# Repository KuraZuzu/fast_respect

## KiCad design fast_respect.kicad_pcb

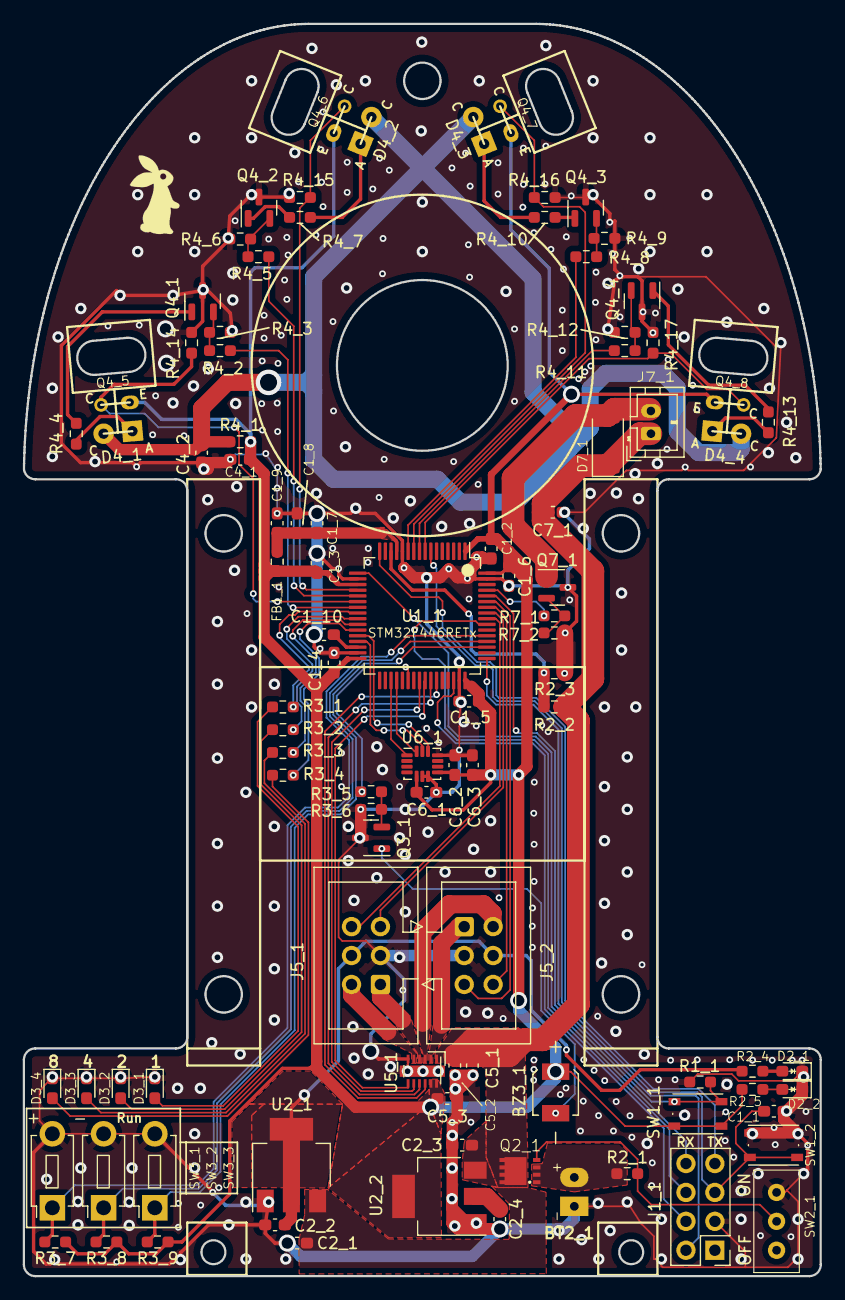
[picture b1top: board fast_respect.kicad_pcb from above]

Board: 2 copper layers, 70.0 x 110.0 mm, 97 parts (0 on the bottom side), 72 nets.

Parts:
BT2_1: Battery; 2sBattery
BZ3_1: SMT-0440-T-HT-R; XDCR_SMT-0440-T-HT-R
C1_1, C1_3, C1_4, C1_5, C1_6, C1_8, C5_2, C5_3, C6_2: 0.1uF; C_0603_1608Metric_Pad1.08x0.95mm_HandSolder
C1_2, C1_10: 4.7uF; C_0603_1608Metric_Pad1.08x0.95mm_HandSolder
C1_7, C6_1: 0.01uF; C_0603_1608Metric_Pad1.08x0.95mm_HandSolder
C1_9, C4_1, C4_2: 1uF; C_0603_1608Metric_Pad1.08x0.95mm_HandSolder
C2_1, C2_3, C5_1, C7_1: 10uF; C_0603_1608Metric_Pad1.08x0.95mm_HandSolder
C2_2, C2_4: 22uF; C_0603_1608Metric_Pad1.08x0.95mm_HandSolder
C6_3: 2.2uF; C_0603_1608Metric_Pad1.08x0.95mm_HandSolder
D2_1: LED_R; LED_0603_1608Metric_Pad1.05x0.95mm_HandSolder
D2_2: LED_Y; LED_0603_1608Metric_Pad1.05x0.95mm_HandSolder
D3_1: LED_B1; LED_0603_1608Metric_Pad1.05x0.95mm_HandSolder
D3_2: LED_B2; LED_0603_1608Metric_Pad1.05x0.95mm_HandSolder
D3_3: LED_B3; LED_0603_1608Metric_Pad1.05x0.95mm_HandSolder
D3_4: LED_B4; LED_0603_1608Metric_Pad1.05x0.95mm_HandSolder
D4_1, D4_2, D4_3, D4_4: SFH4550; DIstance-Sensor_LED_D5.0mm
D7_1: RB080LAM-30TR; D_SOD-128
FB1_1: FerriteBead; R_0603_1608Metric
J1_1: Conn_02x04_Odd_Even; PinHeader_2x04_P2.54mm_Vertical
J5_1, J5_2: Conn_02x03_Odd_Even; IDC-Header_2x03_P2.54mm_Vertical
J7_1: Conn_01x02; JST_PH_B2B-PH-K_1x02_P2.00mm_Vertical
Q2_1: AONM7421; AON7421
Q3_1, Q4_1, Q4_2, Q4_3, Q4_4, Q7_1: IRLML6344T; SOT-23
Q4_5, Q4_6, Q4_7, Q4_8: ST-1KL3A; DIstance-Sensor_PHTR_D5.0mm
R1_1, R3_6, R4_3, R4_6, R4_9, R4_12, R7_2: 10k; R_0603_1608Metric_Pad0.98x0.95mm_HandSolder
R2_1: 100k; R_0603_1608Metric_Pad0.98x0.95mm_HandSolder
R2_2: 2k; R_0603_1608Metric_Pad0.98x0.95mm_HandSolder
R2_3, R3_7, R3_8, R3_9, R4_14, R4_15, R4_16, R4_17: 1k; R_0603_1608Metric_Pad0.98x0.95mm_HandSolder
R2_4: 620; R_0603_1608Metric_Pad0.98x0.95mm_HandSolder
R2_5: 280; R_0603_1608Metric_Pad0.98x0.95mm_HandSolder
R3_1, R3_2, R3_3, R3_4: 100; R_0603_1608Metric_Pad0.98x0.95mm_HandSolder
R3_5, R4_2, R4_5, R4_8, R4_11, R7_1: 10; R_0603_1608Metric_Pad0.98x0.95mm_HandSolder
R4_1: 20; R_0603_1608Metric_Pad0.98x0.95mm_HandSolder
R4_4, R4_7, R4_10, R4_13: 1; R_0603_1608Metric_Pad0.98x0.95mm_HandSolder
SW1_1: BOOT0_SW; SW_Push_1P1T_NO_Vertical_Wuerth_434133025816
SW1_2: NRST_SW; SW_Push_1P1T_NO_Vertical_Wuerth_434133025816
SW2_1: SW_SPDT; SW_Slide_SS12D01G4_AKIZUKI
SW3_1, SW3_2, SW3_3: SW_Push; SW_PUSH_1P1T_6x3.5mm_H4.3_APEM_MJTP1243
U1_1: STM32F446RETx; LQFP-64_10x10mm_P0.5mm
U2_1: AZ1117-5.0; SOT-223-3_TabPin2
U2_2: AZ1117-3.3; SOT-223-3_TabPin2
U5_1: DRV8835DSSR; DRV8835_ThermalExpanded_WSON-12-1EP
U6_1: ICM-42688-P; LGA-14_ExpandPad_3x2.5mm_P0.5mm_LayoutBorder3x4y

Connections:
+3.3V: BZ3_1.LOAD+, C1_2.2, C1_3.2, C1_4.2, C1_5.2, C1_6.2, C2_4.1, C4_1.1, C5_3.2, C6_1.1, C6_2.1, C6_3.1, FB1_1.2, Q4_5.1 (C), Q4_6.1 (C), Q4_7.1 (C), Q4_8.1 (C), R2_5.1, R3_7.1, R3_8.1, R3_9.1, R4_1.2, SW1_1.1, U1_1.1 (VBAT), U1_1.19 (VDD), U1_1.32 (VDD), U1_1.48 (VDD), U1_1.64 (VDD), U2_2.2 (VO), U5_1.11 (Mode), U5_1.12 (VCC), U6_1.5 (VDDIO), U6_1.8 (VDD)
+5V: C2_2.1, J5_1.4, J5_2.4, R2_4.1, U2_1.2 (VO)
+8V: C2_1.1, C2_3.1, C5_1.2, C5_2.1, C7_1.1, D7_1.1 (K), J7_1.1, Q2_1.3 (D), R2_2.1, U2_1.3 (VI), U2_2.3 (VI), U5_1.1 (VM)
BAT_ADC: R2_2.2, R2_3.1, U1_1.14 (PA0)
BOOT0: R1_1.1, SW1_1.2, U1_1.60 (BOOT0)
BUZZER_PWM: R3_5.1, U1_1.38 (PC7)
DIST_ADC_1: Q4_5.2 (E), R4_14.1, U1_1.22 (PA6)
DIST_ADC_2: Q4_6.2 (E), R4_15.1, U1_1.20 (PA4)
DIST_ADC_3: Q4_7.2 (E), R4_16.1, U1_1.10 (PC2)
DIST_ADC_4: Q4_8.2 (E), R4_17.1, U1_1.8 (PC0)
DIST_LED_1: R4_2.1, U1_1.23 (PA7)
DIST_LED_2: R4_5.1, U1_1.21 (PA5)
DIST_LED_3: R4_8.1, U1_1.11 (PC3)
DIST_LED_4: R4_11.1, U1_1.9 (PC1)
ENCODER1_A: J5_1.6, U1_1.56 (PB4)
ENCODER1_B: J5_1.5, U1_1.57 (PB5)
ENCODER2_A: J5_2.6, U1_1.58 (PB6)
ENCODER2_B: J5_2.5, U1_1.59 (PB7)
FAN_MOTOR_PWM: R7_1.1, U1_1.61 (PB8)
GND: BT2_1.2 (-), C1_1.2, C1_2.1, C1_3.1, C1_4.1, C1_5.1, C1_6.1, C1_7.1, C1_8.1, C1_9.1, C1_10.2, C2_1.2, C2_2.2, C2_3.2, C2_4.2, C4_1.2, C4_2.2, C5_1.1, C5_2.2, C5_3.1, C6_1.2, C6_2.2, C6_3.2, C7_1.2, D2_1.1 (K), D2_2.1 (K), D3_1.1 (K), D3_2.1 (K), D3_3.1 (K), D3_4.1 (K), J1_1.3, J5_1.3, J5_2.3, Q3_1.3 (S), Q4_1.3 (S), Q4_2.3 (S), Q4_3.3 (S), Q4_4.3 (S), Q7_1.3 (S), R1_1.2, R2_3.2, R3_6.2, R4_3.2, R4_6.2, R4_9.2, R4_12.2, R4_14.2, R4_15.2, R4_16.2, R4_17.2, R7_2.2, SW1_2.2, SW2_1.1 (A), SW3_1.2, SW3_2.2, SW3_3.2, U1_1.12 (VSSA), U1_1.18 (VSS), U1_1.31 (VSS), U1_1.47 (VSS), U1_1.63 (VSS), U2_1.1 (GND), U2_2.1 (GND), U5_1.6 (GND), U6_1.6 (GND), U6_1.7 (RESV), U6_1.11 (RESV)
GYRO_CS: U1_1.28 (PB2), U6_1.12 (AP_CS)
GYRO_MISO: U1_1.35 (PB14), U6_1.1 (AP_SDO/AP_AD0)
GYRO_MOSI: U1_1.36 (PB15), U6_1.14 (AP_SDA/AP_SDIO/AP_SDI)
GYRO_SCLK: U1_1.29 (PB10), U6_1.13 (AP_SCL/AP_SCLK)
MOTOR1_OUT_1: J5_1.1, U5_1.4 (BOUT1)
MOTOR1_OUT_2: J5_1.2, U5_1.5 (BOUT2)
MOTOR1_PHASE: U1_1.40 (PC9), U5_1.8 (BIN1/B_PHASE)
MOTOR1_PWM: U1_1.41 (PA8), U5_1.7 (BIN2/B_ENABLE)
MOTOR2_OUT_1: J5_2.1, U5_1.2 (AOUT1)
MOTOR2_OUT_2: J5_2.2, U5_1.3 (AOUT2)
MOTOR2_PHASE: U1_1.43 (PA10), U5_1.10 (AIN1/A_PHASE)
MOTOR2_PWM: U1_1.42 (PA9), U5_1.9 (AIN2/A_ENABLE)
NRST: C1_1.1, J1_1.5, SW1_2.1, U1_1.7 (NRST)
unnamed: BT2_1.1 (+), Q2_1.2 (S), R2_1.1
unnamed: D2_1.2 (A), R2_4.2
unnamed: D2_2.2 (A), R2_5.2
unnamed: D3_1.2 (A), R3_1.2
unnamed: D3_2.2 (A), R3_2.2
unnamed: D3_3.2 (A), R3_3.2
unnamed: D3_4.2 (A), R3_4.2
unnamed: C4_2.1, D4_1.2 (A), D4_2.2 (A), D4_3.2 (A), D4_4.2 (A), R4_1.1
unnamed: D4_1.1 (K), R4_4.1
unnamed: D4_2.1 (K), R4_7.1
unnamed: D4_3.1 (K), R4_10.1
unnamed: D4_4.1 (K), R4_13.1
unnamed: D7_1.2 (A), J7_1.2, Q7_1.1 (D)
unnamed: Q2_1.1 (G), R2_1.2, SW2_1.2 (B)
unnamed: BZ3_1.LOAD-, Q3_1.1 (D)
unnamed: Q3_1.2 (G), R3_5.2, R3_6.1
unnamed: Q4_1.1 (D), R4_4.2
unnamed: Q4_1.2 (G), R4_2.2, R4_3.1
unnamed: Q4_2.1 (D), R4_7.2
unnamed: Q4_2.2 (G), R4_5.2, R4_6.1
unnamed: Q4_3.1 (D), R4_10.2
unnamed: Q4_3.2 (G), R4_8.2, R4_9.1
unnamed: Q4_4.1 (D), R4_13.2
unnamed: Q4_4.2 (G), R4_11.2, R4_12.1
unnamed: Q7_1.2 (G), R7_1.2, R7_2.1
unnamed: C1_10.1, U1_1.30 (VCAP_1)
unnamed: C1_7.2, C1_8.2, C1_9.2, FB1_1.1, U1_1.13 (VDDA)
RX: J1_1.8, U1_1.17 (PA3)
SWCLK: J1_1.2, U1_1.49 (PA14)
SWDIO: J1_1.4, U1_1.46 (PA13)
SWO: J1_1.6, U1_1.55 (PB3)
TX: J1_1.7, U1_1.16 (PA2)
UI_LED_1: R3_1.1, U1_1.24 (PC4)
UI_LED_2: R3_2.1, U1_1.25 (PC5)
UI_LED_3: R3_3.1, U1_1.26 (PB0)
UI_LED_4: R3_4.1, U1_1.27 (PB1)
UI_SW_1: R3_7.2, SW3_1.1, U1_1.53 (PC12)
UI_SW_2: R3_8.2, SW3_2.1, U1_1.52 (PC11)
UI_SW_3: R3_9.2, SW3_3.1, U1_1.51 (PC10)

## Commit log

2023-08-23 回路図プロトタイプ作成
2023-08-23 コンデンサの表記を統一
2023-08-23 UIのブザー型番を追記
2023-08-28 モータドライバの型番追加名称変更
2023-08-28 VCAP1のコンデンサの値追加
2023-08-28 距離センサのLED制限抵抗のミスを修正。アノテーションも振り直した。
2023-08-28 電源スイッチ用の回路のPchMOSFETの向き修正
2023-08-28 エンコーダに型番表記追加
2023-08-28 ジャイロセンサのアノテーションがモータドライバと重複していたので修正
2023-08-28 pdfに回路図を生成した
2023-08-29 モータドライバのVMに対して10uFのコンデンサ追加（10uFの値は秋月のモジュールを参考）
2023-08-29 距離センサに強すぎる電流を抑える制限抵抗追加
2023-08-29 距離センサの制限抵抗をsource側からdrain側に変更
2023-08-29 分圧の抵抗値が間違っていたので修正
2023-08-30 アノテーション番号ミスの修正とフットプリント割り当て途中（部品リストも途中生成）
2023-09-01 フェライトビーズに型番追加し、自作パッケージの構成へこう
2023-09-01 自作パッケージのフォルダ名変更
2023-09-01 ジャイロとモータドライバのフットプリント作成して登録、シンボルと紐付けた。
2023-09-04 ブザーSMT-0440のフットプリントとシンボルをインポートして、回路図のシンボルを変更した。
2023-09-04 スイッチ以外のフットプリント割当完了
2023-09-04 秋月電子のスライドスイッチのフットプリントを追加して全てのフットプリント割当も完了
2023-09-07 部品リストをcsvに出力して購入先等の情報を付加した（付加データはまだ途中）
2023-09-08 部品リストのcsv完成
2023-09-08 部品リストの間違いを修正
2023-10-10 吸引ファンのシートとピン追加
2023-10-10 吸引ファンモータのコネクタを追加
2023-10-23 吸引モータ周りの回路修正
2023-11-23 吸引ファンのダイオードの規格やフットプリント割当を完了（完成）
2023-11-23 ネットリスト出力
2023-11-23 R12形式の基板概形DXFデータをファイルに入れた
2023-11-23 基板概形インポートしてシルク印刷線とカット線分けた
2023-11-23 センサのフットプリント配置
2023-11-23 重要パーツ諸々配置した（スイッチの形状や名前とか変えたほうがいいかも）
2023-11-23 色々配置した。これから新たなスイッチのフットプリント作る
2023-11-23 押しボタンスイッチのフットプリント割り当てを変更
2023-11-23 一部のスイッチの名称変更
2023-11-23 ネットリスト更新
2023-11-23 ネットリストを基板に反映
2023-11-23 抵抗とか以外のコア部品配置（バッテリの端子だけ変えた方が良さそう）
2023-11-23 モータ+エンコーダのボックス端子の位置がナットと干渉するので修正
2023-11-24 ジャイロセンサを中央に配置
2023-11-25 2sBatteryのフットプリント作成
2023-11-25 バッテリ端子のフットプリントを割り当ててネットリストに出力して取り込み
2023-11-25 レギュレータ２つのフットプリント割り当てを2ピンが２つあるものに変更した
2023-11-25 gitignoreにKiCAD編集中のファイルを反映した
2023-11-25 グリッド原点のをグローバル座標の原点に戻した
2023-11-26 マイコンの向きを整えた
2023-11-26 UIスイッチ３種類をマイコンピンに割り当て忘れてたので割り当てた
2023-11-26 UIスイッチのピン割り当てをネットリストに反映
2023-11-26 DRV8835のシンボルのピン割当ミスを修正してシンボル回路図修正(6->8)
2023-11-26 DRV8835のピン割当ミスを反映
2023-11-26 DRV8835用にフットプリント作ってシンボルと紐付けた（シンボルも少し更新）
2023-11-26 DRV8835のフットプリントをネットリストに反映させてPCBも更新した
2023-11-26 距離センサのPCB位置を考慮してピン割り当てを変更した（1,2,3,4 -> 4,3,2,1）
2023-11-26 マイコンの位置を再調整
2023-11-26 マイコンのピンアサイン画像を更新
2023-11-26 回路図のPDFを更新
2023-11-26 取り付け角度の画像作成
2023-11-26 ピンアサイン画像のミス修正
2023-11-26 UIのスイッチやLED、書き込み側や電源スイッチの配置を修正
2023-11-27 1、２番台の簡易配置をした
2023-11-27 全体に全体に おおまかな部品配置完了
2023-11-27 色々再配置
2023-11-27 吸引ファンの端子がタイヤのナットや吸引ファンマウンタに干渉しそうなので位置修正
2023-11-27 各配置を決定した。あとは細かい移動や回転のみ
2023-11-27 全ての詳細な位置の数値を決定
2023-11-27 吸引ファンマウンタと吸引ファンケーブルが鑑賞する恐れを考慮して移動
2023-11-27 全ての配置と方向を設定した。あとは配線するだけ（ブランチを切って作業）
2023-11-27 デザインルールの制約を記述
2023-11-28 ネットリストを定義（まだ割り振りしていない）
2023-11-28 モータボックス位置再修正
2023-11-28 配線とビアのサイズ郡を定義した
2023-11-28 更に配線幅追加
2023-11-28 ジャイロとモータドライバの信号線を書いた
2023-11-28 距離センサの信号線まで引いた
2023-11-28 ブザー位置をずらして距離センサのLEDのコンデンサ経由の配線を太くした
2023-11-28 3.3Vのラインまで距離センサをつないだ
2023-11-29 距離センサをGND含めて結んだ
2023-11-29 電源周りを配線勧めた
2023-11-29 モータドライバからのモータ出力配線を引いた
2023-11-29 電源周りを引いた。モータドライバや抵抗、コンデンサの場所を逐次変更した
2023-11-29 色々配線
2023-11-29 3.3V駆動の配線を整えた
2023-11-29 センサとブザー周りの電源修正
2023-11-29 UIスイッチ以外配線
2023-11-29 UI_LED以外を引いた
2023-11-29 全て配線完了（このコミットではUI_LEDを配線）
2023-11-29 DRCエラーを解消（まだ未配線あった）
2023-11-29 配線完了（DRCもシルクとか以外完了） [補足]距離センサのLEDとフォトトラの冗長な電源配線はノイズのるかもしれないから消していいかも。
2023-11-30 数値表示とかを整えた
2023-11-30 一旦距離センサのLEDとフォトトランジスタの電源汚すぎるので削除
2023-11-30 配線し直し。主に距離線センサ関連の電源周り。まだやっていないがベタGNDもだいぶやりやすくなったはず
2023-11-30 ビアの径を変更始め
2023-12-01 印刷面以外は納得の配線した（配線太さやビアも納得してるがモータドライバ出力の0.25区間を短くしたい
2023-12-01 更にビアを追加した。基板左下と右側の外周がベタグランド通じてないので不安が残る
2023-12-03 ベタグランドのために8Vとか吸引ファン関連の素子の位置変えた
2023-12-03 ベタグランドのために電源周り位置変えた
2023-12-04 電源周りを変えて更にベタに強くした
2023-12-04 UIスイッチ周りを整えてベタ強化
2023-12-04 配線を完全に完了した。ベタグランドのビアはこれから打つ
2023-12-04 ビア打つところまで完全に完了したと思う
2023-12-04 ビア打ち直した。これから浮島とかノイズ原因に鳴る半島を削除したい。
2023-12-04 ビアを１つ新たに打った。とりあえずシルクとかのエラーを消したい。
2023-12-04 色々と文字とかのプリント関係を直したが、これ以上は無視設定が必要そう（Fabの値とシルクがかぶる）
2023-12-04 これ以上の印刷面の整えは無理だと思う
2023-12-04 マイコンのピンの印刷情報変更
2023-12-04 UI_LEDの印刷面の数値を変えた
2023-12-04 8Vラインを少し緩やかにした
2023-12-04 ウラ面に機体名のシルク追加
2023-12-07 ビアと配線を広域削除。表示を値からリファレンスにした
2023-12-07 AON7421のフットプリント追加
2023-12-07 AON7421のシンボル作成
2023-12-07 シンボルとフットプリントのピン番号と割り振りを修正
2023-12-07 AON7421のシンボルを差し替えた
2023-12-07 AON7421のシンボル差し替え
2023-12-07 UI関連のアノテーション番号修正
2023-12-07 バッテリのフットぷりとに領域追加
2023-12-08 ネットリストを更新してpcbに反映
2023-12-08 距離センサのLEDとPHTRのフットプリント更新
2023-12-08 距離センサのフットプリントを修正してpcbまで反映
2023-12-08 各パーツと、その近くのコンデンサの配置完了
2023-12-08 これから部品配置を考えつつ配線開始
2023-12-08 シンボルのモータの左右を入れ替え
2023-12-08 モータの出力が入れ替わっていなかったので修正
2023-12-08 モータの左右入れ替えをpcbにも反映
2023-12-08 一旦作業終了
2023-12-10 ２回めのだいたい部品配置完了
2023-12-10 電源スイッチ周りを整えた
2023-12-10 モータアウトプットのラインと領域を引いた
2023-12-10 エンコーダの信号線を引いた
2023-12-10 バッテリ+側のベタ追加
2023-12-10 8Vラインの大本とか引いた
2023-12-10 8V付近の電源周り修正
2023-12-11 モータドライバ信号線配線完了
2023-12-11 モーター信号線少し修正
2023-12-11 マイコンのVDDA周り配線
2023-12-11 取り急ぎ電源周り完了
2023-12-11 色々配置中
2023-12-11 距離センサの向き修正（それと少しの配線追加）
2023-12-11 センサ周りの部品を配置
2023-12-12 距離センサ周り引いた
2023-12-12 左側の3.3vのラインを車体前方まで引いた
2023-12-12 電源周りを整えてUIと書き込み配線以外完成
2023-12-12 UI_LED接続
2023-12-12 書き込みピン配線
2023-12-12 UIスイッチ配線完了
2023-12-12 全て配線して電気的なDRCは消した
2023-12-12 ベタ塗った（ビアない段階だがきれい）
2023-12-12 5Vのサーマルパッドベタの領域増やした
2023-12-12 モータで使うGNDのビアを大きくした
2023-12-12 これからベタGNDのビアを打つ（ついでに一部の配線角度変更）
2023-12-12 とりあえずビア打ち完了
2023-12-12 ビア打ち直し
2023-12-12 ベタGNDをサーマルリリーフにしてビア追加
2023-12-12 ビアの配置と島の削除全て完了（印刷面以外は完成）
2023-12-13 設計図上に移動して原点セット
2023-12-13 印字整え中
2023-12-13 印刷面のサイズ位置とか変更
2023-12-13 ベタGNDの修正（3.3vと8vを重ねてベタ追加）
2023-12-13 吸引ファンのノイズでリセットピンに影響を及ぼす可能性を考慮してある程度戻しつつベタGNDが引けるように微修正
2023-12-13 印刷面整えた
2023-12-13 マイコンの一部のコンデンサの領域かぶりを修正（これからレビュー出す）
2023-12-14 AON7421のフットプリントに裏面シルクが入っていたのを修正
2023-12-14 アールティロゴを追加
2023-12-14 マシン名とアールティロゴシルク追加
2023-12-14 5VラインとベタGND、ビアの修正
2023-12-14 干渉の恐れがある吸引コネクタの位置を変えて配線が浮いている箇所を削除
2023-12-14 ビアとベタGND及び禁止領域を整えた
2023-12-14 シルクの印刷面を修正した。
2023-12-14 表面のRTロゴ位置修正（レビュー３にこれから出す）
2023-12-15 シルクの位置最終調整と、小さいリファレンスを削除（ポチポチ手動）
2023-12-15 吸引ファンコネクタと抵抗がかぶっていたリファレンス修正
2023-12-15 発注形式のデータ出力
2023-12-15 発注データのディレクトリ変更
2023-12-15 発注データを入れるフォルダを度変更してzip形式の発注するやつも作った
2023-12-15 ステンシルを含んでいなかったので再度含んで試した
2023-12-19 発注データのミスを修正
